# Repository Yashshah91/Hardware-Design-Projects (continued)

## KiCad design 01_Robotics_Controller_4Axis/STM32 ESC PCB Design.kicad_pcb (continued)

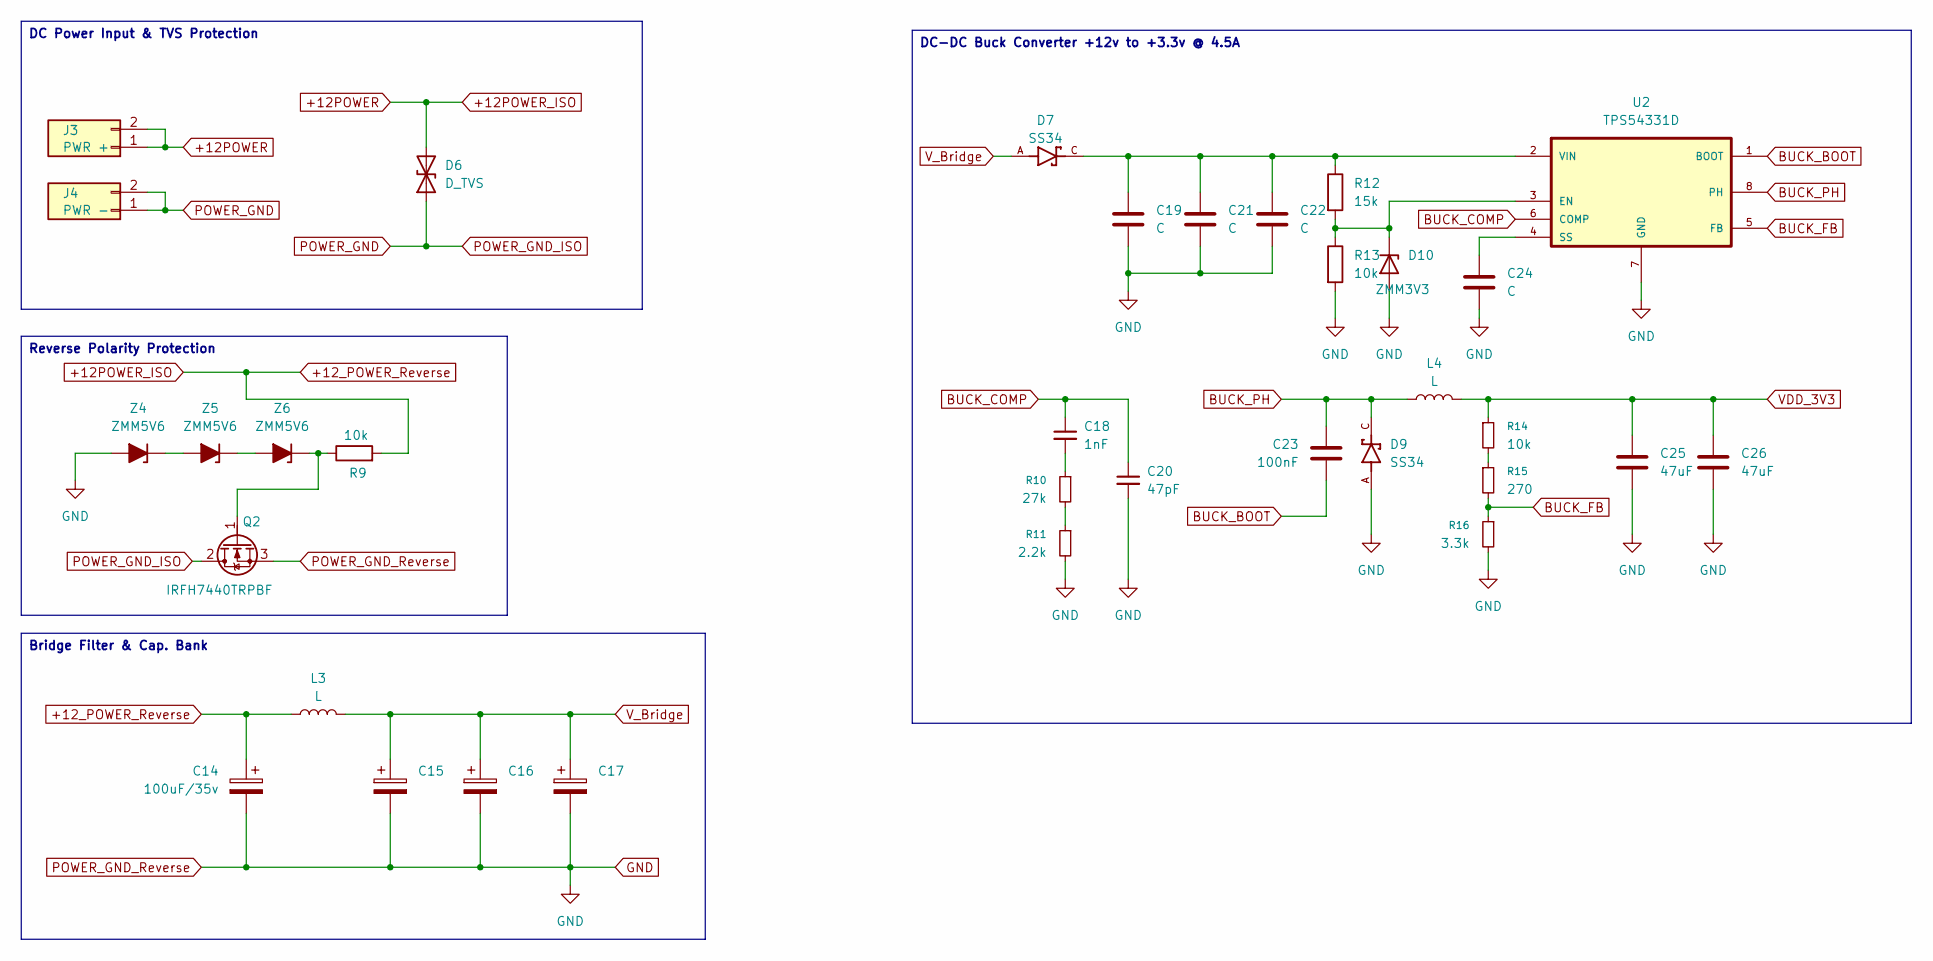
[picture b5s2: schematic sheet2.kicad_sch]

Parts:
C14: 100uF/35v; C_Elec_3x5.4
C15, C16, C17: C_Polarized; C_Elec_3x5.4
C18: 1nF; C_Elec_3x5.4
C19, C21, C22, C24: C; C_Elec_3x5.4
C20: 47pF; C_Elec_3x5.4
C23: 100nF; C_Elec_3x5.4
C25, C26: 47uF; C_Elec_3x5.4
D6: D_TVS; D_T-1_P5.08mm_Horizontal
D7, D9: SS34; DIOM7959X265N; PARTREV 31 Aug 2016
D10: ZMM3V3; D_SMP_DO-220AA
J3: PWR +; PinHeader_1x02_P2.54mm_Vertical
J4: PWR -; PinHeader_1x02_P2.54mm_Vertical
L3, L4: L; L_0805_2012Metric_Pad1.15x1.40mm_HandSolder
Q2: IRFH7440TRPBF; TO-220-3_Vertical
R9, R13, R14: 10k; R_0805_2012Metric
R10: 27k; R_0805_2012Metric
R11: 2.2k; R_0805_2012Metric
R12: 15k; R_0805_2012Metric
R15: 270; R_0805_2012Metric
R16: 3.3k; R_0805_2012Metric
U2: TPS54331D; SOIC127P599X175-8N
Z4, Z5, Z6: ZMM5V6; D_SOD-123

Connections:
+12POWER: C14.1, D6.2 (A2), J3.1, J3.2, L3.1, R9.2
BUCK_BOOT: C23.2, U2.1 (BOOT)
BUCK_COMP: C18.1, C20.1, U2.6 (COMP)
BUCK_FB: R15.2, R16.1, U2.5 (FB)
BUCK_PH: C23.1, D9.C, L4.1, U2.8 (PH)
unnamed: C18.2, R10.1
unnamed: D10.1 (K), R12.2, R13.1, U2.3 (EN)
unnamed: Q2.1 (G), R9.1, Z6.1 (K)
unnamed: R10.2, R11.1
unnamed: R14.2, R15.1
unnamed: C24.1, U2.4 (SS)
unnamed: C19.1, C21.1, C22.1, D7.C, R12.1, U2.2 (VIN)
unnamed: Z4.1 (K), Z5.2 (A)
unnamed: Z5.1 (K), Z6.2 (A)
POWER_GND: D6.1 (A1), J4.1, J4.2, Q2.2 (D)
R_SHUNT1_N: C14.2, C15.2, C16.2, C17.2, C19.2, C20.2, C21.2, C22.2, C24.2, C25.2, C26.2, D9.A, D10.2 (A), Q2.3 (S), R11.2, R13.2, R16.2, U2.7 (GND), Z4.2 (A); also elsewhere on the board
VDD_3V3: C25.1, C26.1, L4.2, R14.1; also elsewhere on the board
V_Bridge: C15.1, C16.1, C17.1, D7.A, L3.2; also elsewhere on the board

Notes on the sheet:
Reverse Polarity Protection
Bridge Filter & Cap. Bank
DC Power Input & TVS Protection
DC-DC Buck Converter +12v to +3.3v @ 4.5A

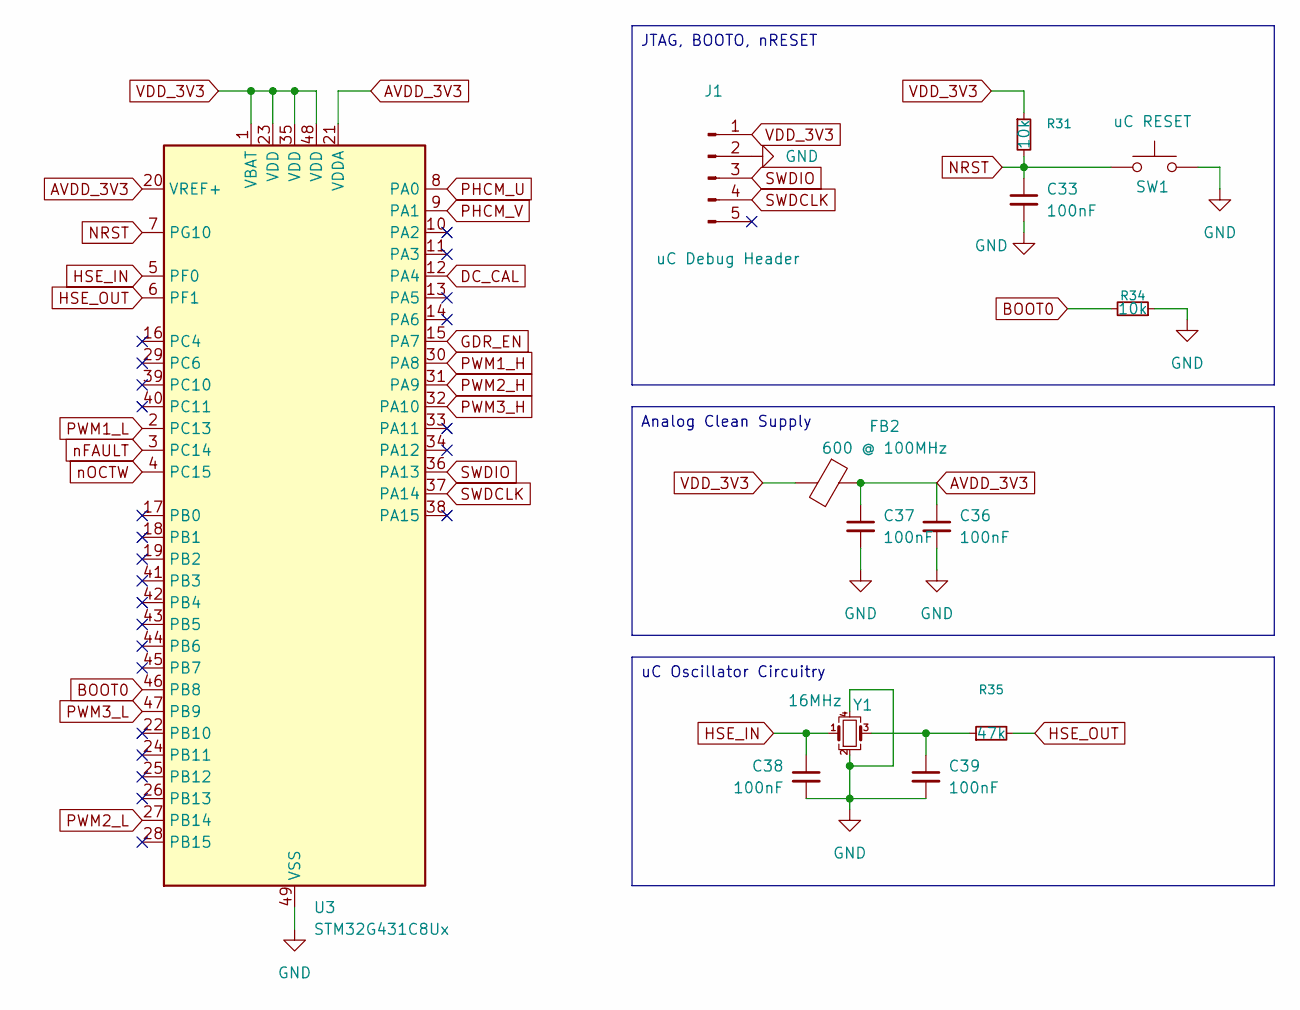
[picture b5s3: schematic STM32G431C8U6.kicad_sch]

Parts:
C33, C36, C37, C38, C39: 100nF; C_Elec_3x5.4
FB2: 600 @ 100MHz; R_0603_1608Metric
J1: uC Debug Header; PinHeader_1x05_P2.54mm_Vertical
R31, R34: 10k; R_0805_2012Metric
R35: 47k; R_0805_2012Metric
SW1: uC RESET; SW_SPST_FSMSM
U3: STM32G431C8Ux; QFN-48-1EP_7x7mm_P0.5mm_EP5.6x5.6mm
Y1: 16MHz; Oscillator_SMD_Abracon_ASCO-4Pin_1.6x1.2mm

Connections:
AVDD_3V3: C36.1, C37.1, FB2.1, U3.20 (VREF+), U3.21 (VDDA)
BOOT0: R34.2, U3.46 (PB8)
DC_CAL: U3.12 (PA4); also elsewhere on the board
GDR_EN: U3.15 (PA7); also elsewhere on the board
HSE_IN: C38.1, U3.5 (PF0), Y1.1
HSE_OUT: R35.2, U3.6 (PF1)
NRST: C33.1, R31.2, SW1.1 (1A), SW1.2 (A), U3.7 (PG10)
unnamed: C39.1, R35.1, Y1.3
PHCM_U: U3.8 (PA0); also elsewhere on the board
PHCM_V: U3.9 (PA1); also elsewhere on the board
PWM1_H: U3.30 (PA8); also elsewhere on the board
PWM1_L: U3.2 (PC13); also elsewhere on the board
PWM2_H: U3.31 (PA9); also elsewhere on the board
PWM2_L: U3.27 (PB14); also elsewhere on the board
PWM3_H: U3.32 (PA10); also elsewhere on the board
PWM3_L: U3.47 (PB9); also elsewhere on the board
R_SHUNT1_N: C33.2, C36.2, C37.2, C38.2, C39.2, J1.2, R34.1, SW1.3 (2A), SW1.4 (B), U3.49 (VSS), Y1.2, Y1.4; also elsewhere on the board
SWDCLK: J1.4, U3.37 (PA14)
SWDIO: J1.3, U3.36 (PA13)
VDD_3V3: FB2.2, J1.1, R31.1, U3.1 (VBAT), U3.23 (VDD), U3.35 (VDD), U3.48 (VDD); also elsewhere on the board
nFAULT: U3.3 (PC14); also elsewhere on the board
nOCTW: U3.4 (PC15); also elsewhere on the board

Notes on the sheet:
uC Oscillator Circuitry
JTAG, BOOTO, nRESET
Analog Clean Supply

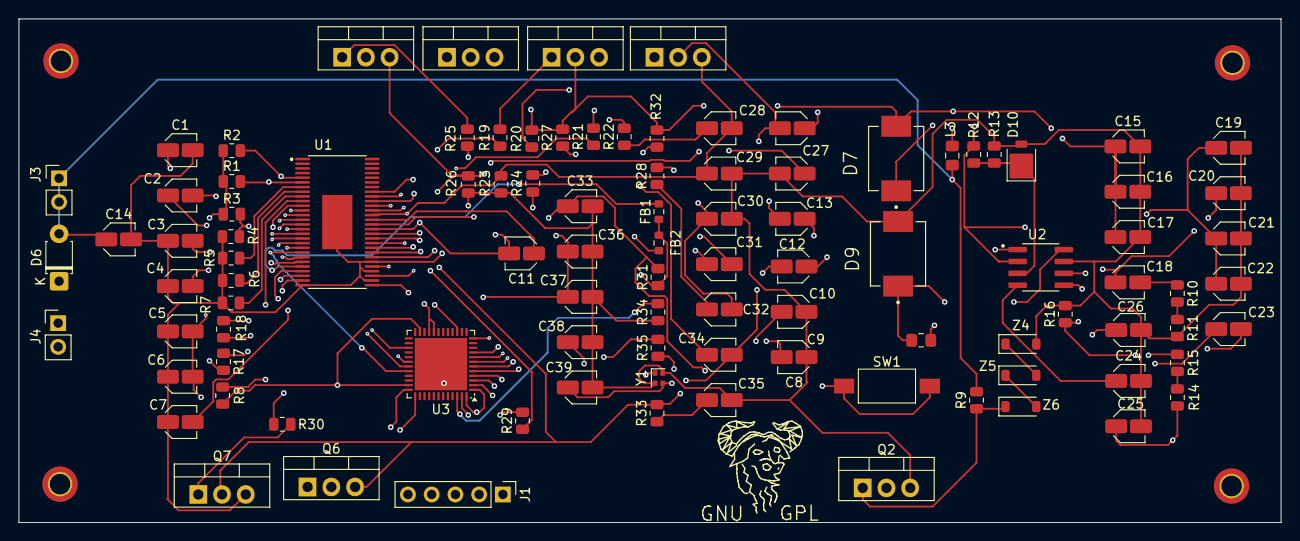
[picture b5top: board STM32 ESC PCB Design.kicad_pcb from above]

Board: 6 copper layers, 135.1 x 53.9 mm, 100 parts (0 on the bottom side), 78 nets.

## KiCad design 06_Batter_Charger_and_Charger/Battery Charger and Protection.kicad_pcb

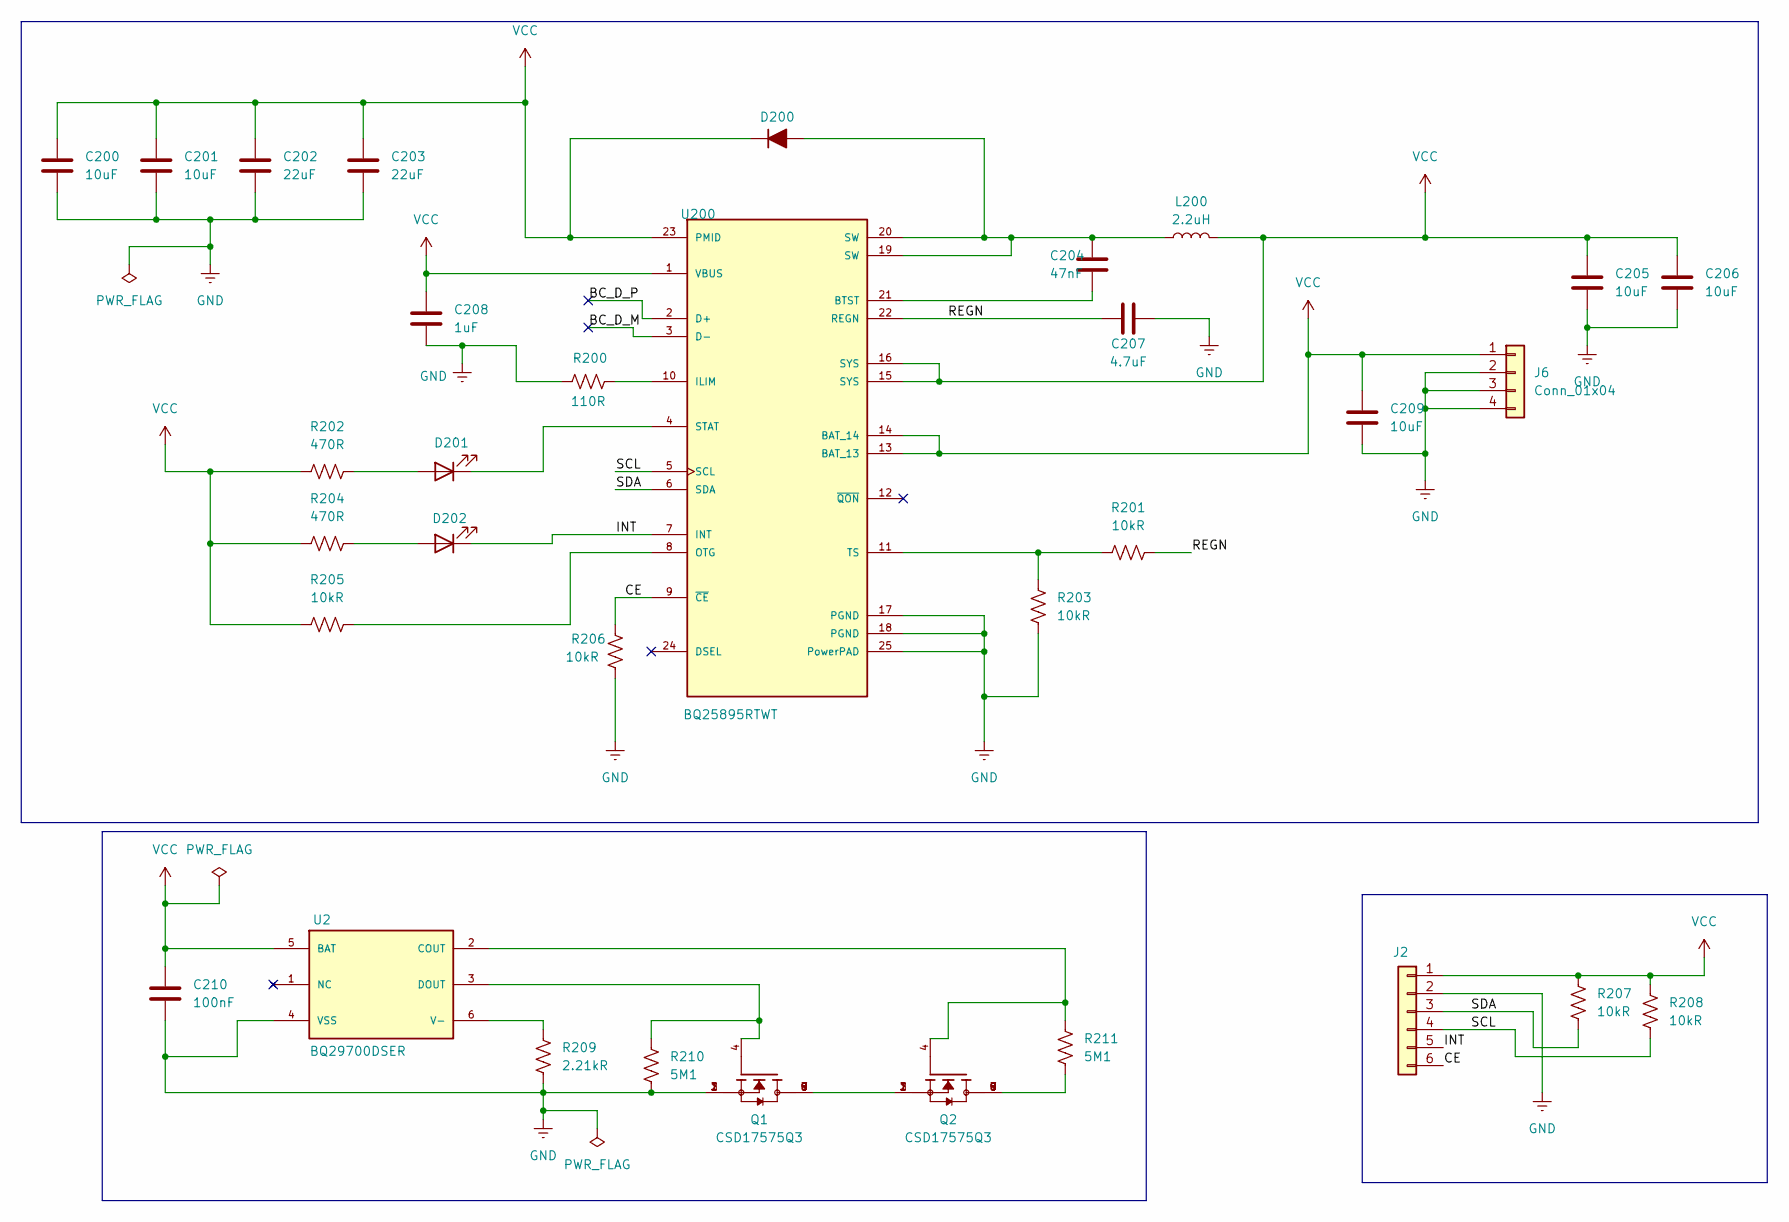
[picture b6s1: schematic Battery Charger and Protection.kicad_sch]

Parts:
C200, C201, C205, C206, C209: 10uF; C_0603_1608Metric
C202, C203: 22uF; C_0603_1608Metric
C204: 47nF; C_0603_1608Metric
C207: 4.7uF; C_0603_1608Metric
C208: 1uF; C_0603_1608Metric
C210: 100nF; C_0603_1608Metric
D200: D_Filled; LED_0603_1608Metric
D201, D202: LED; LED_0603_1608Metric
J2: Conn_01x06; PinHeader_1x06_P2.54mm_Vertical
J6: Conn_01x04; PinHeader_1x04_P2.54mm_Vertical
L200: 2.2uH; L_12x12mm_H6mm
Q1, Q2: CSD17575Q3; TRANS_CSD17575Q3; PARTREV A
R200: 110R; R_0603_1608Metric
R201, R203, R205, R206, R207, R208: 10kR; R_0603_1608Metric
R202, R204: 470R; R_0603_1608Metric
R209: 2.21kR; R_0603_1608Metric
R210, R211: 5M1; R_0603_1608Metric
U2: BQ29700DSER; SON50P150X150X80-6N; PARTREV G
U200: BQ25895RTWT; QFN50P400X400X80-25N; PARTREV B

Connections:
/BC_D_M: U200.3 (D-)
/BC_D_P: U200.2 (D+)
/CE: J2.6, R206.2, U200.9 (~CE)
/INT: D202.1 (K), J2.5, U200.7 (INT)
/REGN: C207.1, R201.1, U200.22 (REGN)
/SCL: J2.4, R208.2, U200.5 (SCL)
/SDA: J2.3, R207.2, U200.6 (SDA)
GND: C200.2, C201.2, C202.2, C203.2, C205.2, C206.2, C207.2, C208.2, C209.2, C210.2, J2.2, J6.2, J6.3, J6.4, Q1.1, Q1.2, Q1.3, R200.1, R203.1, R206.1, R209.2, R210.2, U2.4 (VSS), U200.17 (PGND), U200.18 (PGND), U200.25 (PowerPAD)
unnamed: C204.2, D200.2 (A), L200.1, U200.19 (SW), U200.20 (SW)
unnamed: D201.2 (A), R202.2
unnamed: D201.1 (K), U200.4 (STAT)
unnamed: D202.2 (A), R204.2
unnamed: Q1.5, Q1.6, Q1.7, Q1.8, Q1.9, Q2.1, Q2.2, Q2.3
unnamed: Q2.5, Q2.6, Q2.7, Q2.8, Q2.9, R211.2
unnamed: Q2.4, R211.1, U2.2 (COUT)
unnamed: Q1.4, R210.1, U2.3 (DOUT)
unnamed: R209.1, U2.6 (V-)
unnamed: C204.1, U200.21 (BTST)
unnamed: R200.2, U200.10 (ILIM)
unnamed: R205.2, U200.8 (OTG)
unnamed: R201.2, R203.2, U200.11 (TS)
VCC: C200.1, C201.1, C202.1, C203.1, C205.1, C206.1, C208.1, C209.1, C210.1, D200.1 (K), J2.1, J6.1, L200.2, R202.1, R204.1, R205.1, R207.1, R208.1, U2.5 (BAT), U200.1 (VBUS), U200.13 (BAT_13), U200.14 (BAT_14), U200.15 (SYS), U200.16 (SYS), U200.23 (PMID)

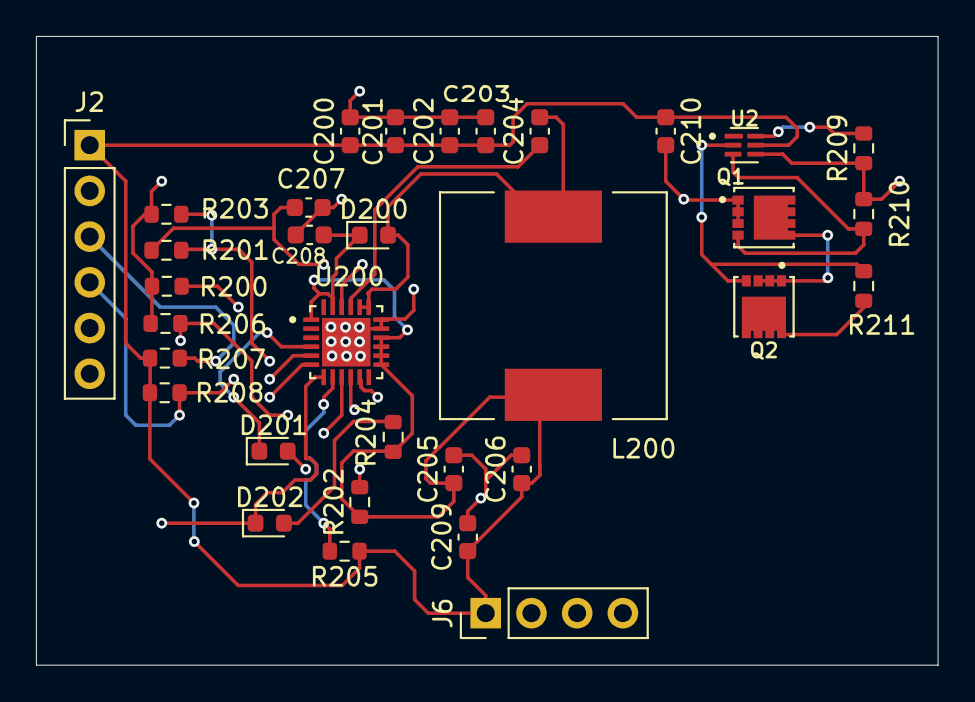
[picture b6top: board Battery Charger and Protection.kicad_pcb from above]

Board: 4 copper layers, 50.1 x 34.9 mm, 33 parts (0 on the bottom side), 20 nets.

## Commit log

2025-09-29 Create temp
2025-09-29 files upload
2025-09-29 file upload
